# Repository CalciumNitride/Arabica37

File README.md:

# Arabica3/7

A split keyboard with 3x6 column staggered keys, 1 pinkey and 3 thumb keys.

* Keyboard Maintainer: [CalciumNitride](https://github.com/CalciumNitride)
* Hardware Supported: Arabica3/7 PCB, Pro Micro

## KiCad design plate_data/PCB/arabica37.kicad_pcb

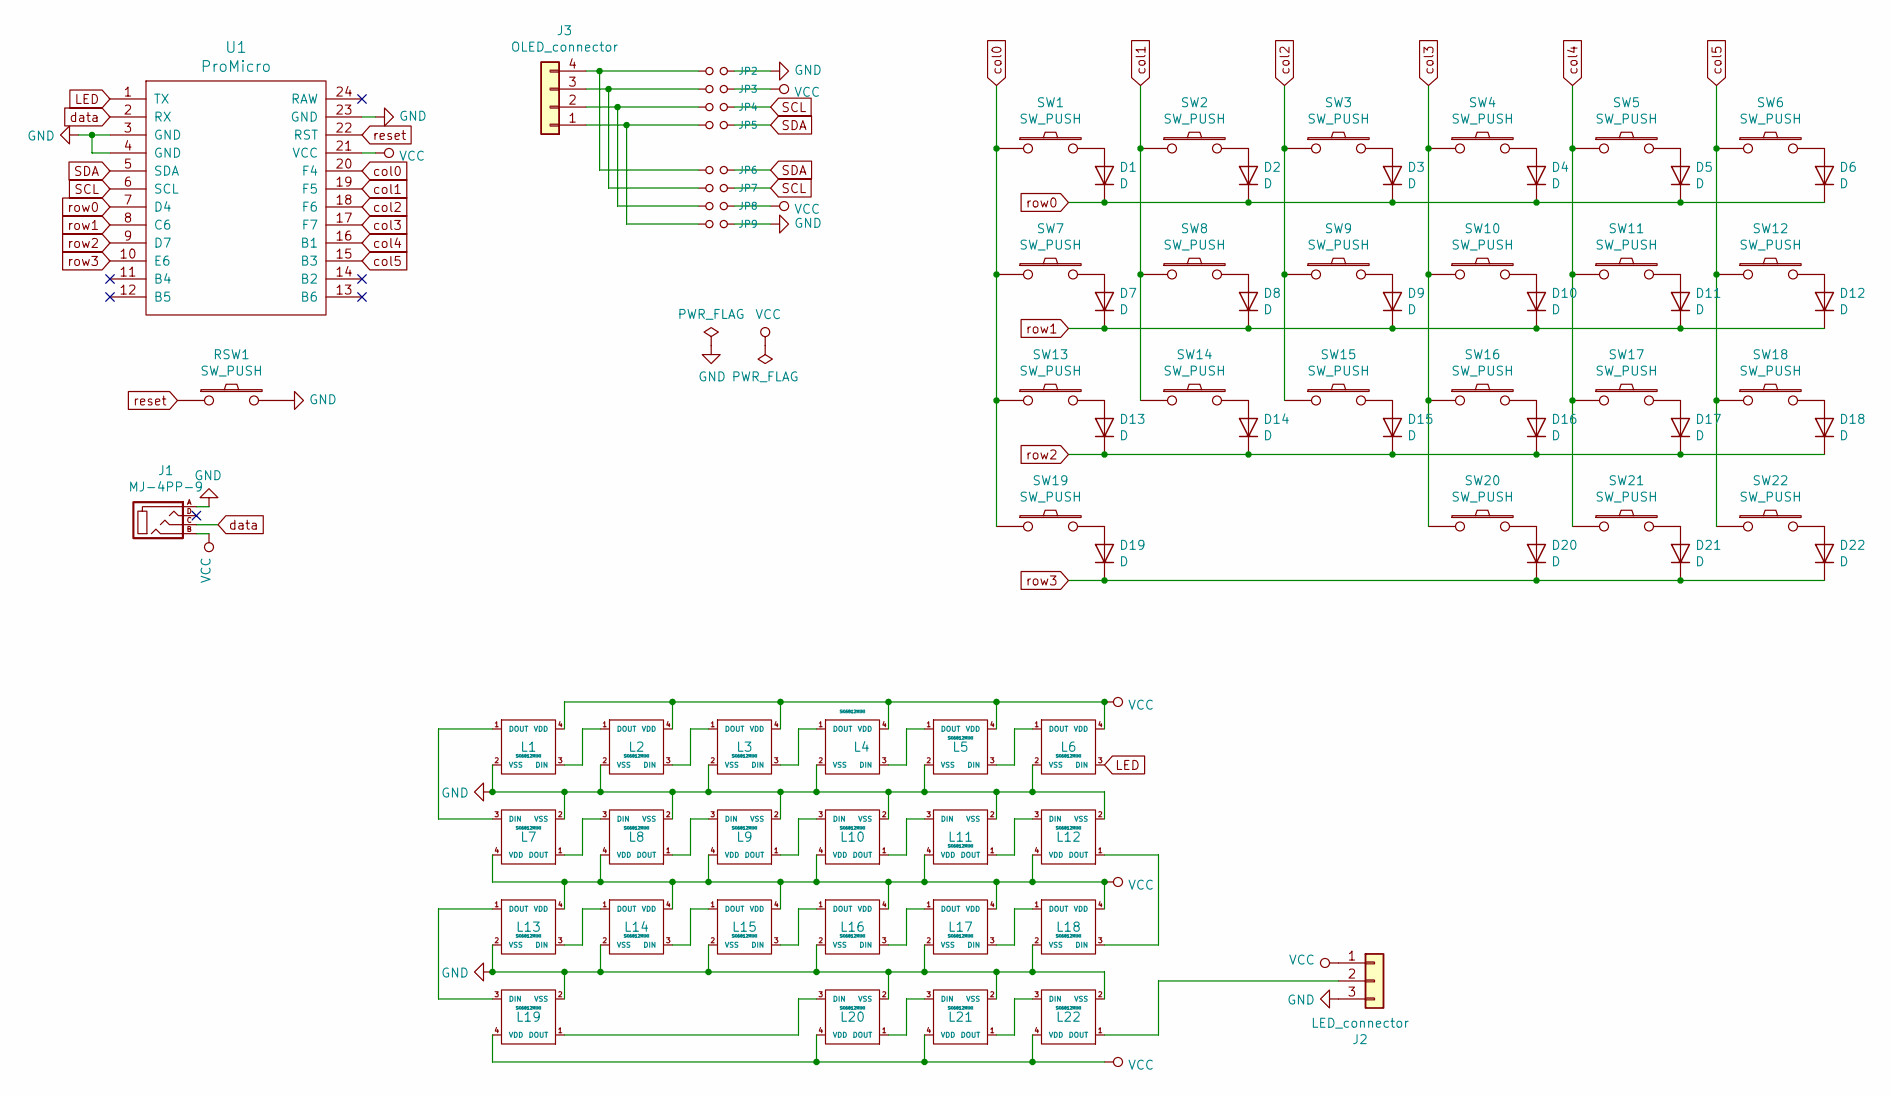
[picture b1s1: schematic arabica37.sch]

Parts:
D1, D2, D3, D4, D5, D6, D7, D8, D9, D10, D11, D12, D13, D14, D15, D16, D17, D18, D19, D20, D21, D22: D; Diode-dual
J1: MJ-4PP-9
J2: LED_connector; StripLED_rev_LR
J3: OLED_connector; OLED
JP2, JP3, JP4, JP5, JP6, JP7, JP8, JP9: Jumper_NO_Small; Jumper
L1, L2, L3, L4, L5, L6, L7, L8, L9, L10, L11, L12, L13, L14, L15, L16, L17, L18, L19, L20, L21, L22: SK6812MINI; SK6812MINI_rev
RSW1: SW_PUSH; SW_Tactile_SPST_Angled_MJTP1117
SW1, SW2, SW3, SW4, SW5, SW6, SW7, SW8, SW9, SW10, SW11, SW12, SW13, SW14, SW15, SW16, SW17, SW18, SW20, SW21, SW22: SW_PUSH; CherryMX_Hotswap
SW19: SW_PUSH; CherryMX_Hotswap_2U
U1: ProMicro; ProMicro_v2

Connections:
GND: J1.A, J2.3, JP2.2, JP9.2, L1.2 (VSS), L2.2 (VSS), L3.2 (VSS), L4.2 (VSS), L5.2 (VSS), L6.2 (VSS), L7.2 (VSS), L8.2 (VSS), L9.2 (VSS), L10.2 (VSS), L11.2 (VSS), L12.2 (VSS), L13.2 (VSS), L14.2 (VSS), L15.2 (VSS), L16.2 (VSS), L17.2 (VSS), L18.2 (VSS), L19.2 (VSS), L20.2 (VSS), L21.2 (VSS), L22.2 (VSS), RSW1.2, U1.3 (GND), U1.4 (GND), U1.23 (GND); also elsewhere on the board
LED: L6.3 (DIN), U1.1 (TX)
unnamed: D1.2 (A), SW1.2
unnamed: D2.2 (A), SW2.2
unnamed: D3.2 (A), SW3.2
unnamed: D4.2 (A), SW4.2
unnamed: D5.2 (A), SW5.2
unnamed: D6.2 (A), SW6.2
unnamed: D7.2 (A), SW7.2
unnamed: D8.2 (A), SW8.2
unnamed: D9.2 (A), SW9.2
unnamed: D10.2 (A), SW10.2
unnamed: D11.2 (A), SW11.2
unnamed: D12.2 (A), SW12.2
unnamed: D13.2 (A), SW13.2
unnamed: D14.2 (A), SW14.2
unnamed: D15.2 (A), SW15.2
unnamed: D16.2 (A), SW16.2
unnamed: D17.2 (A), SW17.2
unnamed: D18.2 (A), SW18.2
unnamed: D19.2 (A), SW19.2
unnamed: D20.2 (A), SW20.2
unnamed: D21.2 (A), SW21.2
unnamed: D22.2 (A), SW22.2
unnamed: J2.2, L22.1 (DOUT)
unnamed: J3.1, JP5.1, JP9.1
unnamed: J3.2, JP4.1, JP8.1
unnamed: J3.3, JP3.1, JP7.1
unnamed: J3.4, JP2.1, JP6.1
unnamed: L1.1 (DOUT), L7.3 (DIN)
unnamed: L1.3 (DIN), L2.1 (DOUT)
unnamed: L2.3 (DIN), L3.1 (DOUT)
unnamed: L3.3 (DIN), L4.1 (DOUT)
unnamed: L4.3 (DIN), L5.1 (DOUT)
unnamed: L5.3 (DIN), L6.1 (DOUT)
unnamed: L7.1 (DOUT), L8.3 (DIN)
unnamed: L8.1 (DOUT), L9.3 (DIN)
unnamed: L10.1 (DOUT), L11.3 (DIN)
unnamed: L9.1 (DOUT), L10.3 (DIN)
unnamed: L11.1 (DOUT), L12.3 (DIN)
unnamed: L12.1 (DOUT), L18.3 (DIN)
unnamed: L13.1 (DOUT), L19.3 (DIN)
unnamed: L13.3 (DIN), L14.1 (DOUT)
unnamed: L14.3 (DIN), L15.1 (DOUT)
unnamed: L15.3 (DIN), L16.1 (DOUT)
unnamed: L16.3 (DIN), L17.1 (DOUT)
unnamed: L17.3 (DIN), L18.1 (DOUT)
unnamed: L19.1 (DOUT), L20.3 (DIN)
unnamed: L20.1 (DOUT), L21.3 (DIN)
unnamed: L21.1 (DOUT), L22.3 (DIN)
SCL: JP4.2, JP7.2, U1.6 (SCL)
SDA: JP5.2, JP6.2, U1.5 (SDA)
VCC: J1.B, J2.1, JP3.2, JP8.2, L1.4 (VDD), L2.4 (VDD), L3.4 (VDD), L4.4 (VDD), L5.4 (VDD), L6.4 (VDD), L7.4 (VDD), L8.4 (VDD), L9.4 (VDD), L10.4 (VDD), L11.4 (VDD), L12.4 (VDD), L13.4 (VDD), L14.4 (VDD), L15.4 (VDD), L16.4 (VDD), L17.4 (VDD), L18.4 (VDD), L19.4 (VDD), L20.4 (VDD), L21.4 (VDD), L22.4 (VDD), U1.21 (VCC)
col0: SW1.1, SW7.1, SW13.1, SW19.1, U1.20 (F4)
col1: SW2.1, SW8.1, SW14.1, U1.19 (F5)
col2: SW3.1, SW9.1, SW15.1, U1.18 (F6)
col3: SW4.1, SW10.1, SW16.1, SW20.1, U1.17 (F7)
col4: SW5.1, SW11.1, SW17.1, SW21.1, U1.16 (B1)
col5: SW6.1, SW12.1, SW18.1, SW22.1, U1.15 (B3)
data: J1.C, U1.2 (RX)
reset: RSW1.1, U1.22 (RST); also elsewhere on the board
row0: D1.1 (K), D2.1 (K), D3.1 (K), D4.1 (K), D5.1 (K), D6.1 (K), U1.7 (D4)
row1: D7.1 (K), D8.1 (K), D9.1 (K), D10.1 (K), D11.1 (K), D12.1 (K), U1.8 (C6)
row2: D13.1 (K), D14.1 (K), D15.1 (K), D16.1 (K), D17.1 (K), D18.1 (K), U1.9 (D7)
row3: D19.1 (K), D20.1 (K), D21.1 (K), D22.1 (K), U1.10 (E6)

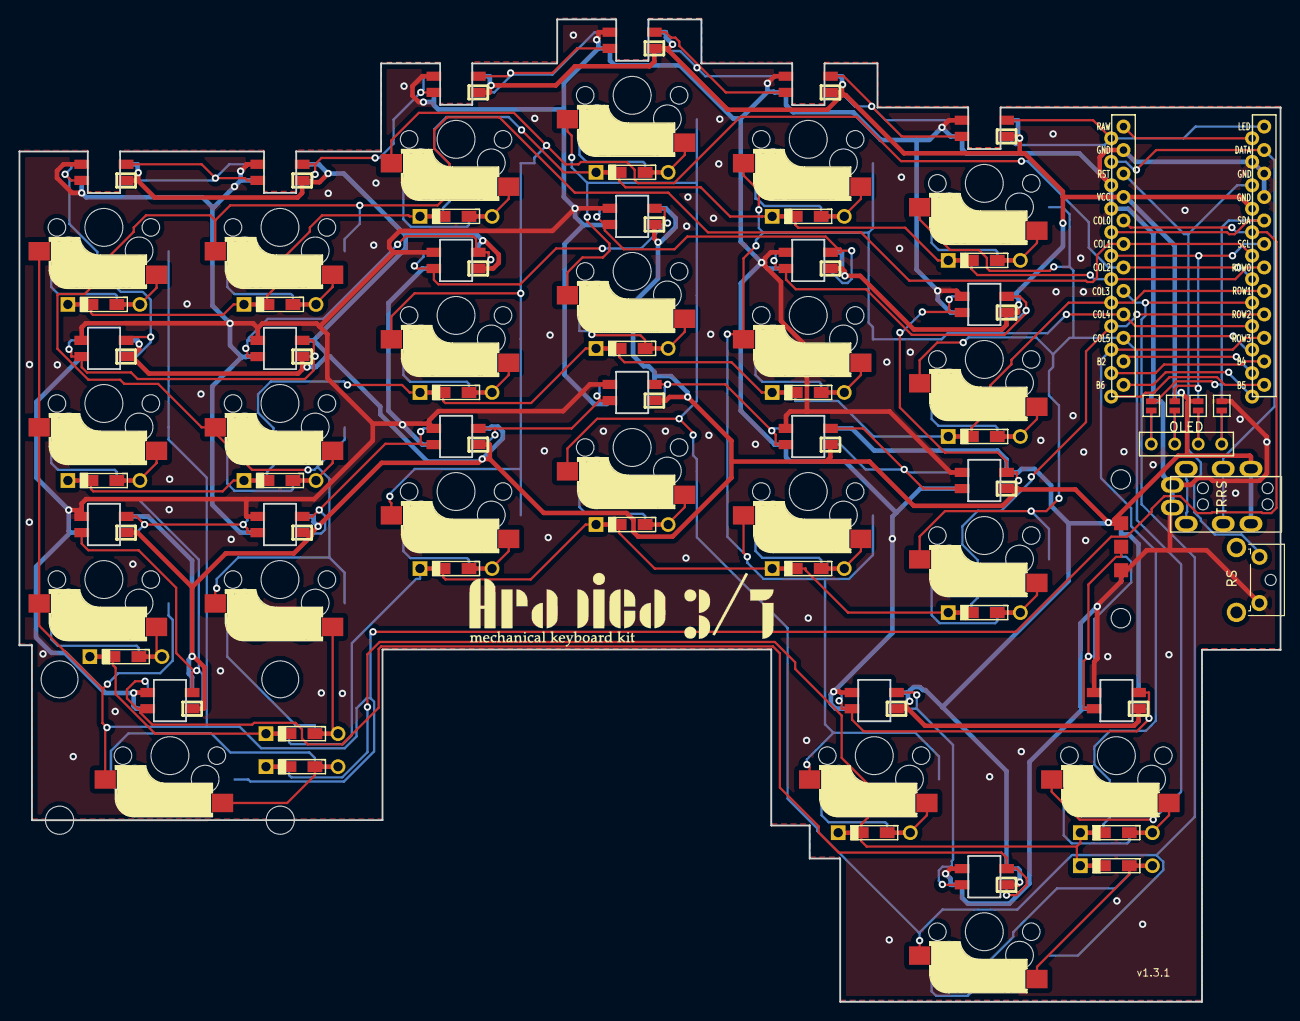
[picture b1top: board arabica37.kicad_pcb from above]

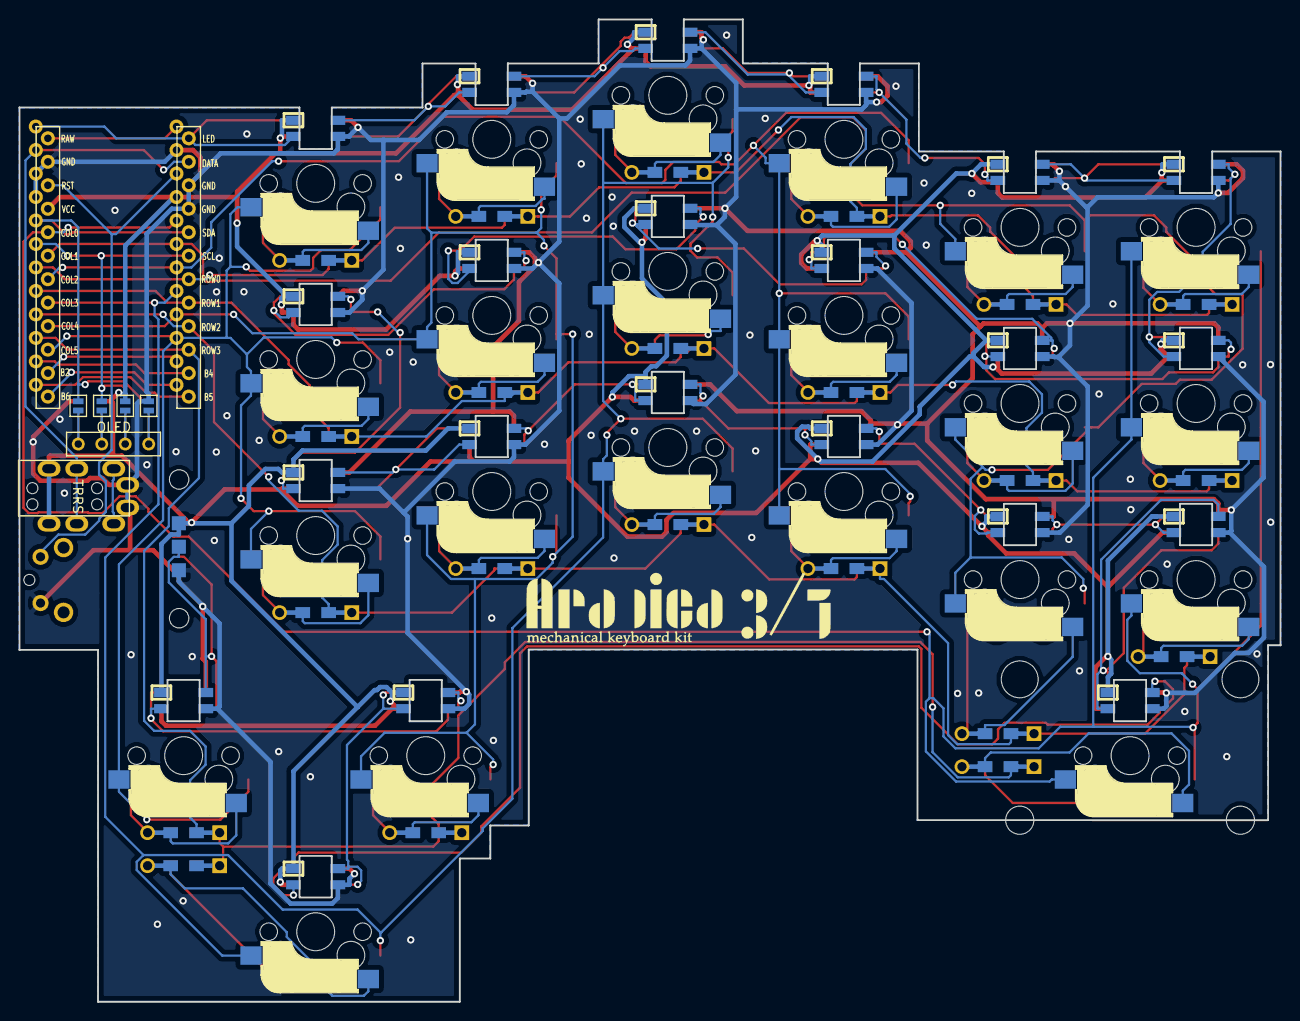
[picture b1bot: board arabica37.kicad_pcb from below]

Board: 2 copper layers, 136.4 x 106.3 mm, 82 parts (6 on the bottom side), 65 nets.

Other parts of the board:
Ga***: LOGO; arabica37_logo
RS: SW_PUSH; SW_Tactile_SPST_Angled_MJTP1117
a: a; HOLE_M2
e: a; HOLE_M2

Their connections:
GND: RS.2; also elsewhere on the board
reset: RS.1; also elsewhere on the board

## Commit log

2019-10-24 Rename buildguide.md to v1.2_buildguide.md
2019-10-24 Rename v1.2_buildguide.md to v1.2buildguide.md
2020-05-17 remove old firmware
2020-05-17 add new firmware
2020-05-17 organize files
2020-05-19 no message
2020-05-19 organize plate_data files and add 'ProMicro-cover.ai'
2026-03-12 Revise README for Arabica3/7 project
    Updated project name and added description and links.
2026-03-12 Update README to remove QMK setup instructions
    Removed unnecessary instructions for QMK setup.
